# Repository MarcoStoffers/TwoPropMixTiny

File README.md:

# TwoPropMixTiny
## 2-prop mixer for RC model with 2 drive props, rudder and bow thruster

- Depending on the direction, the curve inner motor is braked or controlled to reverse (adjustable via a setup). The sensitivity at which curve position the mixer should intervene can be set via a potentiometer.
- If a bow thruster is also used, this can also be used to support cornering (can also be switched on via setup). Up to which speed the bow thruster intervenes can be adjusted with the 2nd potentiometer.

## Requirement
- All motors (right-hand drive, left-hand drive, bow thruster) must have their own speed controller and the two drives must run equally (the model does not pull away to one side when driving straight ahead).
- The model can be "normally" driven via an RC remote control (Forward | Reverse | Left | Right | Bow Thruster Left | Bow Thruster Right)
- The power supply for the module (4.5V - 5.5V) is guaranteed (see manual / only german at the moment).

## Base
The module is based on a microchip ATtiny841 which is programmed via the [Arduino IDE](https://arduino.cc/). To use the microcontroller, the extension of [Spence Konde](https://github.com/SpenceKonde/ATTinyCore) is necessary. Programming is done without a bootloader directly via the ISP contacts on the bottom side of the PCB with an AVR programmer.

## License
The project is licensed under the Creative Common License. A rebuild for private or non-profit associations is desired, commercial rebuild or distribution I forbid. If someone should develop the mixer further, I ask for the naming of the original project.

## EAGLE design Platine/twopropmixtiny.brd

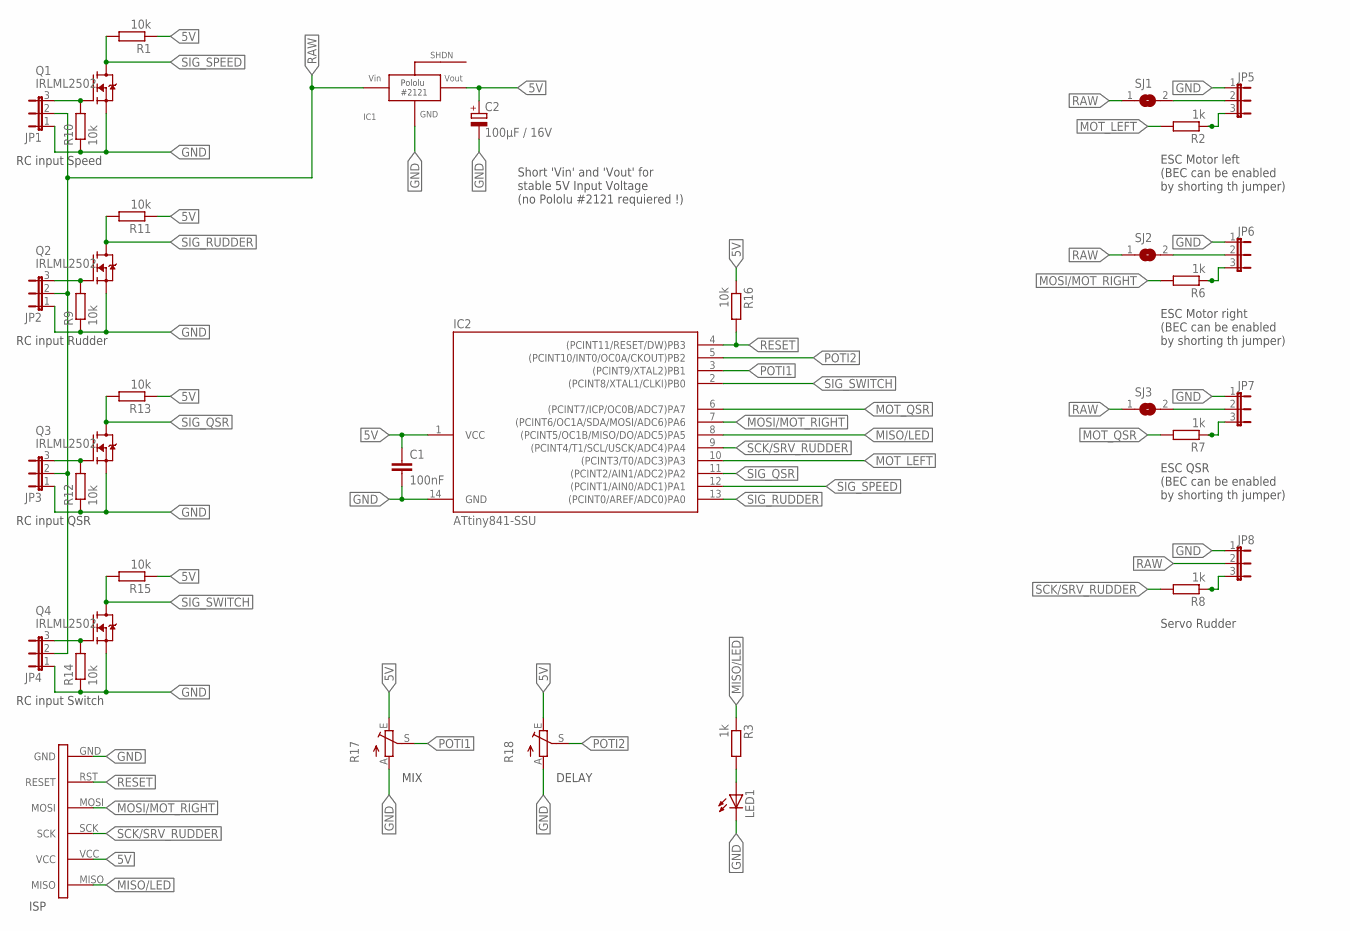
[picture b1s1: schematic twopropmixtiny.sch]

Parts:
C1: 100nF; C0805
C2: 100µF / 16V; PANASONIC_D
IC1: POLOLU2121
IC2: ATtiny841-SSU; SOIC14
JP1, JP2, JP3, JP4, JP5, JP6, JP7, JP8: JP2EJP2_OHNE_TEXT; JP2
LED1: LEDCHIPLED_0805; CHIPLED_0805
Q1, Q2, Q3, Q4: IRLML2502; SOT23-3
R1, R9, R10, R11, R12, R13, R14, R15, R16: 10k; R0805
R2, R3, R6, R7, R8: 1k; R0805
R17, R18: TRIM_EU-PT10; PT-10
SJ1, SJ2, SJ3: SJ
U$1: ISP

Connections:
5V: C1.1, C2.+, IC1.VOUT, IC2.1 (VCC), R1.1, R11.1, R13.1, R15.1, R16.1, R17.E, R18.E, U$1.VCC
GND: C1.2, C2.-, IC1.GND, IC2.14 (GND), JP1.1, JP2.1, JP3.1, JP4.1, JP5.1, JP6.1, JP7.1, JP8.1, LED1.C, Q1.2 (S), Q2.2 (S), Q3.2 (S), Q4.2 (S), R9.1, R10.1, R12.1, R14.1, R17.A, R18.A, U$1.GND
MISO/LED: IC2.8 ((PCINT5/OC1B/MISO/DO/ADC5)PA5), R3.1, U$1.MISO
MOSI/MOT_RIGHT: IC2.7 ((PCINT6/OC1A/SDA/MOSI/ADC6)PA6), R6.2, U$1.MOSI
MOT_LEFT: IC2.10 ((PCINT3/T0/ADC3)PA3), R2.2
MOT_QSR: IC2.6 ((PCINT7/ICP/OC0B/ADC7)PA7), R7.2
unnamed: JP1.3, Q1.1 (G), R10.2
unnamed: JP5.3, R2.1
unnamed: JP2.3, Q2.1 (G), R9.2
unnamed: LED1.A, R3.2
unnamed: JP3.3, Q3.1 (G), R12.2
unnamed: JP6.3, R6.1
unnamed: JP7.3, R7.1
unnamed: JP8.3, R8.1
unnamed: JP5.2, SJ1.2
unnamed: JP6.2, SJ2.2
unnamed: JP7.2, SJ3.2
unnamed: JP4.3, Q4.1 (G), R14.2
POTI1: IC2.3 ((PCINT9/XTAL2)PB1), R17.S
POTI2: IC2.5 ((PCINT10/INT0/OC0A/CKOUT)PB2), R18.S
RAW: IC1.VIN, JP1.2, JP2.2, JP3.2, JP4.2, JP8.2, SJ1.1, SJ2.1, SJ3.1
RESET: IC2.4 ((PCINT11/RESET/DW)PB3), R16.2, U$1.RST (RESET)
SCK/SRV_RUDDER: IC2.9 ((PCINT4/T1/SCL/USCK/ADC4)PA4), R8.2, U$1.SCK
SIG_QSR: IC2.11 ((PCINT2/AIN1/ADC2)PA2), Q3.3 (D), R13.2
SIG_RUDDER: IC2.13 ((PCINT0/AREF/ADC0)PA0), Q2.3 (D), R11.2
SIG_SPEED: IC2.12 ((PCINT1/AIN0/ADC1)PA1), Q1.3 (D), R1.2
SIG_SWITCH: IC2.2 ((PCINT8/XTAL1/CLKI)PB0), Q4.3 (D), R15.2

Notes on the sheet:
RC input Speed
RC input Rudder
RC input QSR
RC input Switch
ISP
Short 'Vin' and 'Vout' for stable 5V Input Voltage (no Pololu #2121 requiered !)
MIX
DELAY
ESC Motor left (BEC can be enabled by shorting th jumper)
ESC Motor right (BEC can be enabled by shorting th jumper)
ESC QSR (BEC can be enabled by shorting th jumper)
Servo Rudder

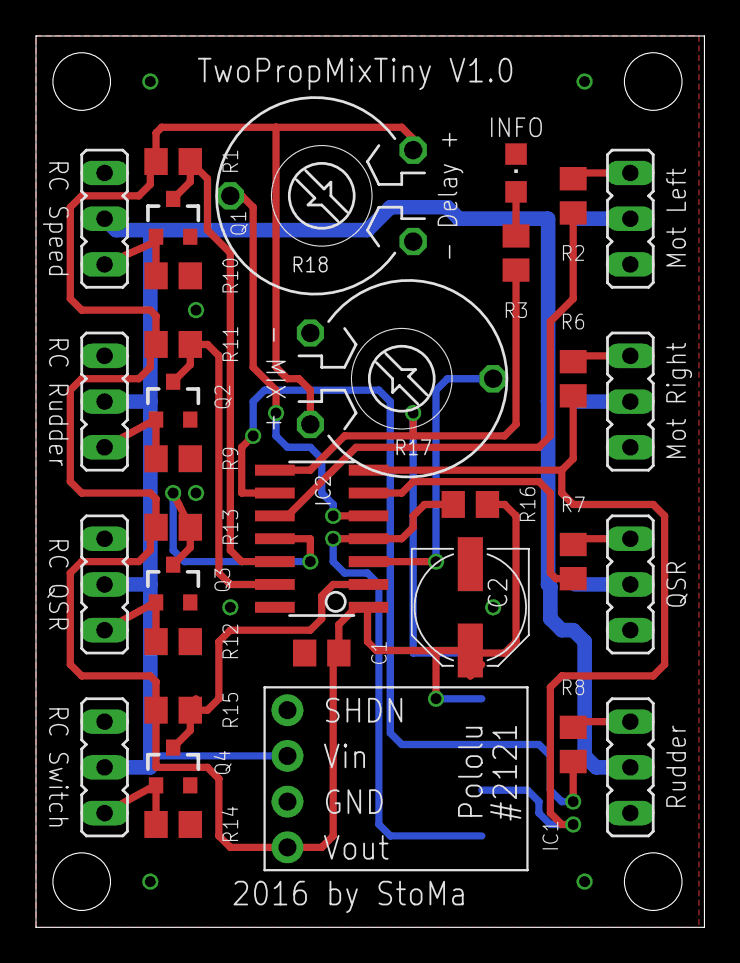
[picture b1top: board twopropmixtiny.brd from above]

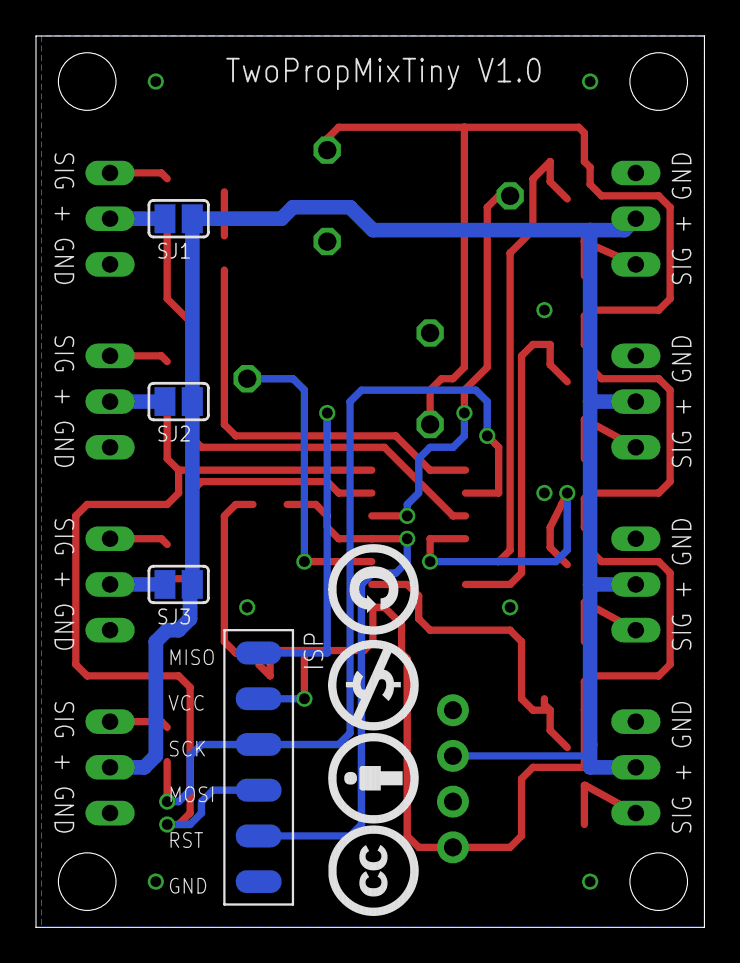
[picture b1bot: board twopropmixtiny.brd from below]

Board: 2 copper layers, 37.1 x 49.5 mm, 37 parts (4 on the bottom side), 27 nets.

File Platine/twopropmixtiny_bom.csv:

"Qty";"Value";"Device";"Package";"Parts";"Description";"";
"8";"";"JP2EJP2_OHNE_TEXT";"JP2";"JP1, JP2, JP3, JP4, JP5, JP6, JP7, JP8";"JUMPER";"";
"1";"";"LEDCHIPLED_0805";"CHIPLED_0805";"LED1";"LED";"";
"3";"";"SJ";"SJ";"SJ1, SJ2, SJ3";"SMD solder JUMPER";"";
"2";"";"TRIM_EU-PT10";"PT-10";"R17, R18";"POTENTIOMETER";"";
"1";"100nF";"C-EUC0805";"C0805";"C1";"CAPACITOR, European symbol";"";
"1";"100µF / 16V";"CPOL-EUD";"PANASONIC_D";"C2";"POLARIZED CAPACITOR, European symbol";"";
"9";"10k";"R-EU_R0805";"R0805";"R1, R9, R10, R11, R12, R13, R14, R15, R16";"RESISTOR, European symbol";"";
"5";"1k";"R-EU_R0805";"R0805";"R2, R3, R6, R7, R8";"RESISTOR, European symbol";"";
"1";"ATtiny841-SSU";"TINY24/44/84-SSU";"SOIC14";"IC2";"";"";
"4";"IRLML2502";"IRLML2502";"SOT23-3";"Q1, Q2, Q3, Q4";"International Rectifier";"";
"1";"ISP";"ISP";"ISP";"U$1";"";"";
"1";"POLOLU2121";"POLOLU2121";"POLOLU2121";"IC1";"";"";

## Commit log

2019-09-09 New version with support for FlySky Receivers
    FlySky Receivers give out all channels at the same time. This causes in a permanent Interrupt which slows down the Main Loop. New vrsion will clear the Interrupt flag if more than one channel trigger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

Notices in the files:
parts and their libraries:
xmaker: Licensing: CC v3.0 Attribution-Share Alike
http://creativecommons.org/licenses/by-sa/3.0
